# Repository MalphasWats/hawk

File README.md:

# hawk
Small ARM dev board based on ATSAMD10.

This repository takes a step-by-step look at creating a simple ATSAMD10-based dev-board using KiCAD.

## Contents

### Designing the PCB

1. [Getting Started - Creating a Schematic.](https://github.com/MalphasWats/hawk/blob/master/articles/creating-the-schematic.markdown)
2. [Adding Battery Power.](https://github.com/MalphasWats/hawk/blob/master/articles/adding-battery-power.markdown)
3. [Footprints & Net-lists.](https://github.com/MalphasWats/hawk/blob/master/articles/footprints-and-netlists.markdown)
4. [Creating a PCB.](https://github.com/MalphasWats/hawk/blob/master/articles/creating-a-pcb.markdown)
5. [Aside: Designing a Board Outline.](https://github.com/MalphasWats/hawk/blob/master/articles/designing-board-outline.markdown)
6. [Component Layout.](https://github.com/MalphasWats/hawk/blob/master/articles/component-layout.markdown)
7. [Laying Traces.](https://github.com/MalphasWats/hawk/blob/master/articles/laying-traces.markdown)
8. [Filled Zones.](https://github.com/MalphasWats/hawk/blob/master/articles/filling-zones.markdown)
9. [Silkscreen.](https://github.com/MalphasWats/hawk/blob/master/articles/silkscreen.markdown)
10. [PCB Manufacture.](https://github.com/MalphasWats/hawk/blob/master/articles/pcb-manufacture.markdown)

### Assembly
11. [Assembly.](https://github.com/MalphasWats/hawk/blob/master/articles/assembly.markdown)

### Programming

...

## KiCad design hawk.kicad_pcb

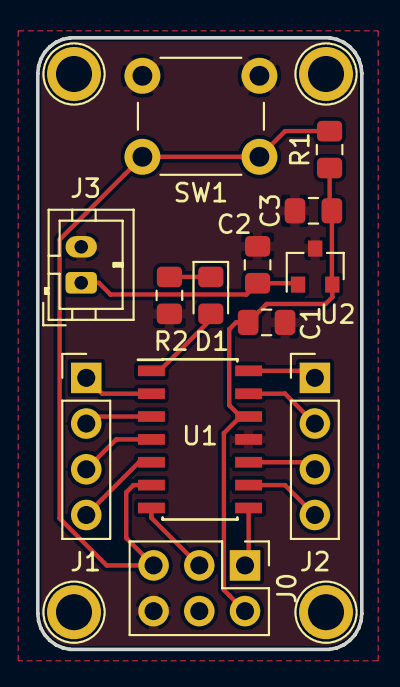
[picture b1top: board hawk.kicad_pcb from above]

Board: 2 copper layers, 18.0 x 34.0 mm, 13 parts (0 on the bottom side), 16 nets.

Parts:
C1: 0.1uF; C_0805_2012Metric_Pad1.15x1.40mm_HandSolder
C2, C3: 1uF; C_0805_2012Metric_Pad1.15x1.40mm_HandSolder
D1: LED_ALT; LED_0805_2012Metric_Pad1.15x1.40mm_HandSolder
J0: SWD_PGM; PinHeader_2x03_P2.54mm_Vertical
J1: GPIO_A; PinHeader_1x04_P2.54mm_Vertical
J2: GPIO_B; PinHeader_1x04_P2.54mm_Vertical
J3: Battery; JST_PH_B2B-PH-K_1x02_P2.00mm_Vertical
R1: 10k; R_0805_2012Metric_Pad1.15x1.40mm_HandSolder
R2: 1k; R_0805_2012Metric_Pad1.15x1.40mm_HandSolder
SW1: SW_Push; SW_PUSH_6mm
U1: ATSAMD10C14A-SS; SOIC-14_3.9x8.7mm_P1.27mm
U2: AP7333-33SRG-7; SOT-23

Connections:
+3V3: C1.1, C3.1, J0.2, R1.1, U1.12, U2.2
+BATT: C2.1, J3.1, U2.1
GND: C1.2, C2.2, C3.2, J0.6, J3.2, R2.1, SW1.2, U1.11, U2.3
GPIO_1: J1.1, U1.2
GPIO_2: J1.2, U1.3
GPIO_3: J1.3, U1.4
GPIO_4: J1.4, U1.5
GPIO_5: J2.1, U1.14
GPIO_6: J2.2, U1.13
GPIO_7: J2.3, U1.10
GPIO_8: J2.4, U1.9
LED: D1.2, U1.1
unnamed: D1.1, R2.2
SWCLK: J0.3, U1.7
SWDIO: J0.1, U1.8
reset: J0.5, R1.2, SW1.1, U1.6

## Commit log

2019-04-22 initial implementation
2019-04-22 initial page
2019-04-22 testing large screenshots
2019-04-22 Table of contents added
2019-04-22 renamed all schematic screenshots
2019-04-22 add links
2019-04-22 renamed all screenshots
2019-04-22 pcb page template
2019-04-22 Added pages
2019-04-22 board manfuacture writeup
2019-04-22 add picture
2019-04-22 added end bit
2019-04-24 Written up to power symbols.
2019-04-24 Written up to first annotate
2019-04-24 Switch and LED circuit
2019-04-24 Completed creating schematic part 1
2019-04-24 typo
2019-04-25 Written next part
2019-04-25 trim screenshots
2019-04-25 added text to connect to regulator
2019-04-25 added link to switch
2019-04-25 note
2019-04-25 Part 3 done.
2019-05-02 Part 4 done.
2019-05-02 Part 5
2019-05-02 image not link
2019-05-02 Page templates
2019-05-02 added info about update pcb from schematic
2019-05-02 added more info
2019-05-12 add cache file
2019-05-12 inital blink import
2019-05-12 article notes
2019-07-09 tidy lib
2019-07-10 streamlining lib
2019-07-13 bitbang spi oled test
2019-07-14 48MHz clock
2019-07-17 component layout
2019-07-17 drawings explanation.
2019-07-17 drc note
2019-07-17 Added assemby article
2019-07-17 added link
2019-09-21 fixed a typo
2019-10-16 experimenting with speed
2019-11-17 horrible oled code for SSD1351
2020-03-04 added pcb capabilites image reference
